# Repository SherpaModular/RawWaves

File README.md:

## Raw Waves v2

Raw Waves v2 is a sample player that functions much like a live radio. Audio sample files may be placed on a MicroSD card, and arranged into "banks" (like channels) which you may select either manually through the panel knobs, or via CV. File formats supported include RAW and WAV files.

The module is functionally identical to the popular "Raw Waves" module, and its predecessor, "Radio Music" by Tom Whitwell of Music Thing Modular. These previous modules are no longer available, having been built upon the now-discontinued Teensy 3 microcontroller.

Raw Waves v2 has been completely redesigned to use the Teensy 4 platform. Because the module uses the Teensy 4 microcontroller, the "Raw Waves v2" will not be compatible with other alternative firmware made for Radio Music (e.g. 'Chord Organ').

Raw Waves v2 still supports all of the settings in the SETTINGS.TXT file that you came to know and love in the earlier models. If you haven't played with the settings, you really should!

#### Specifications
Audio output: 16-bit audio output, with hardware anti-alias filtering.
Dimensions: 4 hp, 21mm deep.
Power specifications: Requires +12v (at 100 mA) and -12v (at 10 mA). The module features several protections against accidental reverse power connection: First, a keyed 10-pin Eurorack standard connector, second, automatically resetting fuses, and thirdly, protection diodes.
CV Inputs are designed for 0-5v, with reasonable over/undervoltage protection built-in.

#### Compiling the code
My preference is to use Visual Studio Code:
1. Install the Microsoft "Arduino for Visual Studio Code" extension
2. Add the Teensy packages. You can accomplish this in the "Arduino for Visual Studio Code" extension settings by adding the URL https://www.pjrc.com/teensy/package_teensy_index.json to the "Arduino: Additional Urls, Additional URLs for 3rd party packages." setting.
3. The following file contents, placed into the repo under the filename .vscode\arduino.json helps with other details:
```
{
    "sketch": "Software\\RawWavesV2\\RawWavesV2.ino",
    "configuration": "usb=serial,speed=600,opt=o2std,keys=en-us",
    "board": "teensy:avr:teensy40",
    "output": "ArduinoOutput\\RawWavesV2",
    "port": "COM3"
}
```
4. In VS Code, activate the Command Palette (typically by pressing F1), and choose "Ardunio: Verify".
5. If all codes well, the compiled output should appear in the repo directory, under ArduinoOutput\RawWavesV2

#### License  
Raw Waves is Open Hardware. It is a derivate work of ["Radio Music", by Tom Whitwell](https://github.com/TomWhitwell/RadioMusic). 
All hardware and software design in this project is Creative Commons licensed by Jim Mulvey: [CC-BY-SA: Attribution / ShareAlike](https://creativecommons.org/licenses/by-sa/3.0/)
If you use any work in this project, you should credit Tom Whitwell and me, and you must republish any changes you make under the same license.
This license does permit commercial use of these designs, but consider getting in touch before selling anything.
This project includes work from the [Teensy](https://www.pjrc.com/teensy/) project, which is not covered by this license.

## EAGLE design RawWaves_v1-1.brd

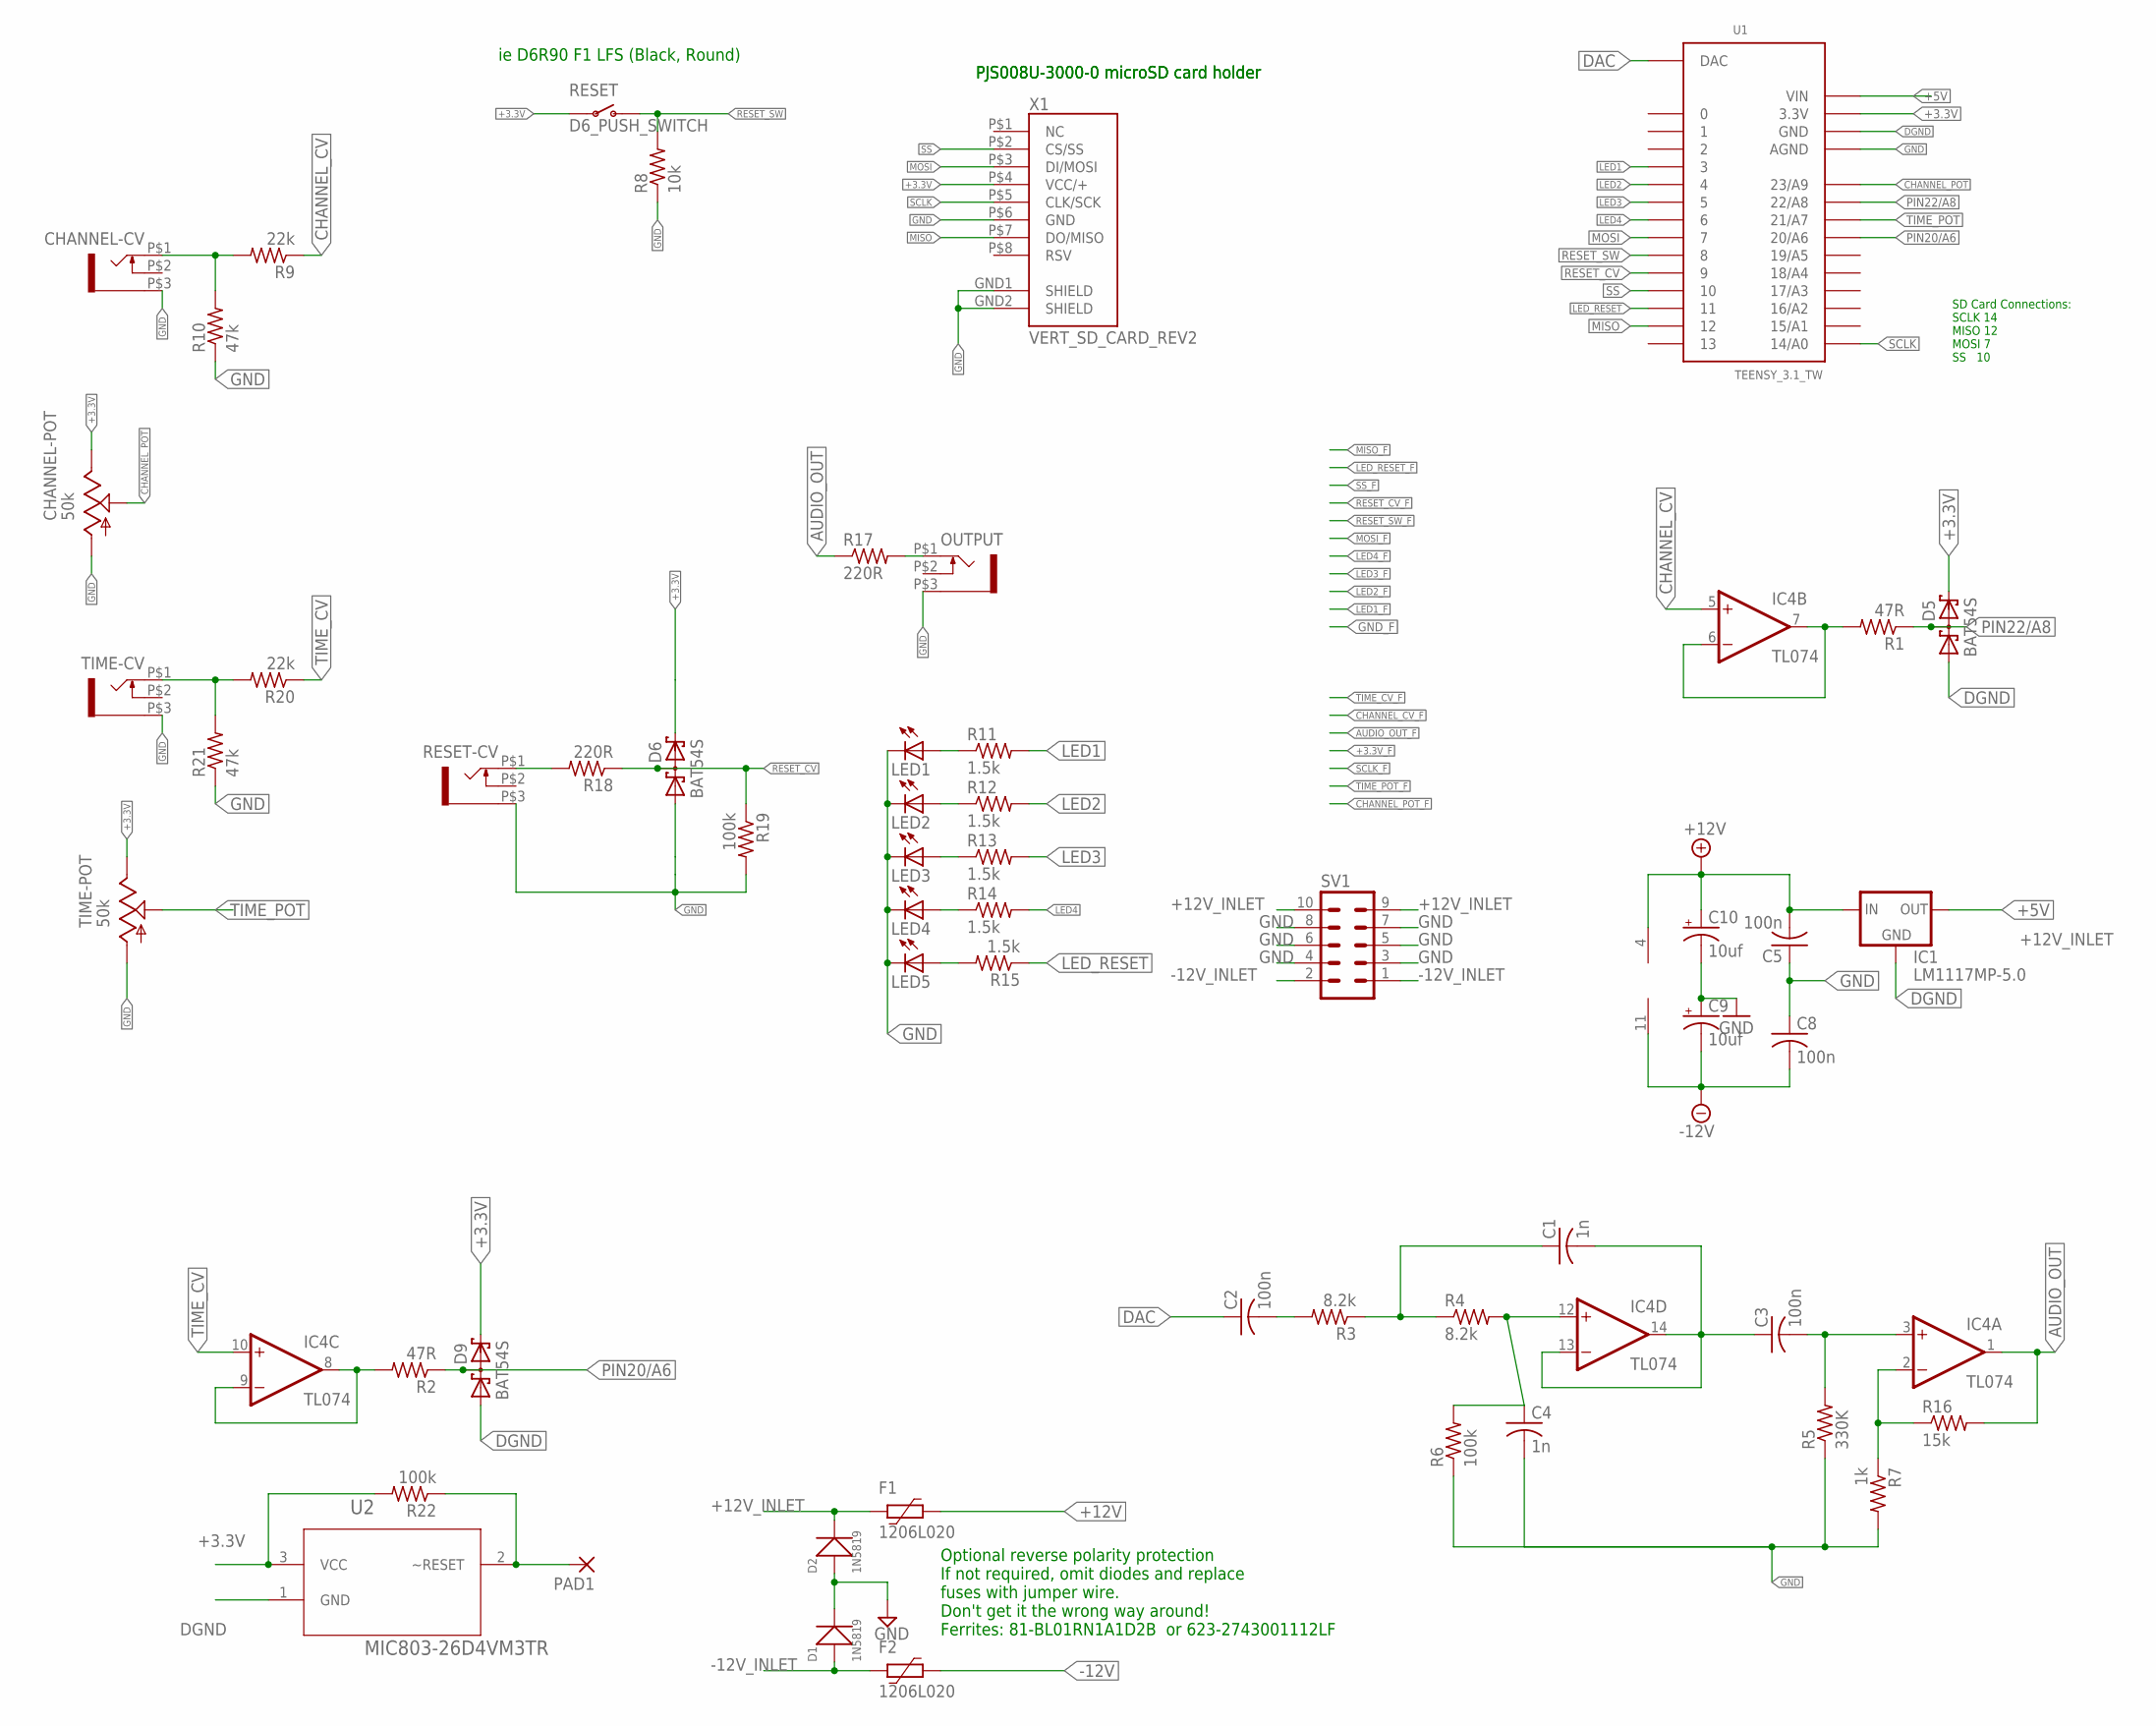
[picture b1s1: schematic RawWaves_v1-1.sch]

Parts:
C1, C4: 1n; C0805
C2, C3, C5, C8: 100n; C0805
C9, C10: 10uf; PANASONIC_B
CHANNEL-CV: WQP-PJ301M-12_JACK
CHANNEL-POT: 50k; EVUF
D1, D2: 1N5819; SOD-123
D5, D6, D9: BAT54S; SOT23
F1, F2: 1206L020; 1206L
IC1: LM1117MP-5.0; SOT223
IC4: TL074; SO14
LED1, LED2, LED3, LED4, LED5: LED3MM
OUTPUT: WQP-PJ301M-12_JACK
PAD1: 1,6/0,9
R1, R2: 47R; R0805
R3, R4: 8.2k; R0805
R5: 330K; R0805
R6, R19, R22: 100k; R0805
R7: 1k; R0805
R8: 10k; R0805
R9, R20: 22k; R0805
R10, R21: 47k; R0805
R11, R12, R13, R14, R15: 1.5k; R0805
R16: 15k; R0805
R17, R18: 220R; R0805
RESET: D6_PUSH_SWITCH; D6_BUTTON_RND
RESET-CV: WQP-PJ301M-12_JACK
SV1: 10_PIN_HEADER; MA05-2
TIME-CV: WQP-PJ301M-12_JACK
TIME-POT: 50k; EVUF
U1: TEENSY_3.1_TW
U2: MIC803-26D4VM3TR; SOT95P232X110-3N
X1: VERT_SD_CARD_REV2; VERT_MICROSD_REV2

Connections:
+3.3V: CHANNEL-POT.3 (E), D5.2 (C2), D6.2 (C2), D9.2 (C2), R22.2, RESET.P$3, RESET.P$4, TIME-POT.3 (E), U1.3.3V, U2.3 (VCC), X1.P$4 (VCC/+)
+5V: IC1.2 (OUT), IC1.4 (OUT), U1.VIN
+12V: C5.2, C10.+, F1.1, IC1.3 (IN), IC4.4 (V+)
+12V_INLET: D2.-, F1.2, SV1.9, SV1.10
-12V: C8.2, C9.-, F2.1, IC4.11 (V-)
-12V_INLET: D1.+, F2.2, SV1.1, SV1.2
AUDIO_OUT: IC4.1 (OUT), R16.2, R17.1
CHANNEL_CV: IC4.5 (+IN), R9.1
CHANNEL_POT: CHANNEL-POT.2 (S), U1.23/A9
DAC: C2.1, U1.DAC
DGND: D5.1 (A1), D9.1 (A1), IC1.1 (GND), U1.GND, U2.1 (GND)
GND: C4.2, C5.1, C8.1, C9.+, C10.-, CHANNEL-CV.P$3 (1), CHANNEL-POT.1 (A), D1.-, D2.+, D6.1 (A1), LED1.K (C), LED2.K (C), LED3.K (C), LED4.K (C), LED5.K (C), OUTPUT.P$3 (1), R5.1, R6.1, R7.2, R8.1, R10.1, R19.2, R21.1, RESET-CV.P$3 (1), SV1.3, SV1.4, SV1.5, SV1.6, SV1.7, SV1.8, TIME-CV.P$3 (1), TIME-POT.1 (A), U1.AGND, X1.GND1 (SHIELD), X1.GND2 (SHIELD), X1.P$6 (GND)
LED1: R11.2, U1.3
LED2: R12.2, U1.4
LED3: R13.2, U1.5
LED4: R14.2, U1.6
LED_RESET: R15.1, U1.11
MISO: U1.12, X1.P$7 (DO/MISO)
MOSI: U1.7, X1.P$3 (DI/MOSI)
unnamed: IC4.6 (-IN), IC4.7 (OUT), R1.2
unnamed: C4.1, IC4.12 (+IN), R4.2, R6.2
unnamed: OUTPUT.P$1 (2), R17.2
unnamed: C1.1, R3.1, R4.1
unnamed: C1.2, C3.1, IC4.13 (-IN), IC4.14 (OUT)
unnamed: C3.2, IC4.3 (+IN), R5.2
unnamed: IC4.2 (-IN), R7.1, R16.1
unnamed: IC4.8 (OUT), IC4.9 (-IN), R2.2
unnamed: CHANNEL-CV.P$1 (2), R9.2, R10.2
unnamed: C2.2, R3.2
unnamed: LED2.A, R12.1
unnamed: LED4.A, R14.1
unnamed: LED3.A, R13.1
unnamed: R18.2, RESET-CV.P$1 (2)
unnamed: LED1.A, R11.1
unnamed: LED5.A, R15.2
unnamed: PAD1.1, R22.1, U2.2 (~RESET)
PIN20/A6: D9.3 (C1A2), R2.1, U1.20/A6
PIN22/A8: D5.3 (C1A2), R1.1, U1.22/A8
RESET_CV: D6.3 (C1A2), R18.1, R19.1, U1.9
RESET_SW: R8.2, RESET.P$1 (O), RESET.P$2 (O), U1.8
SCLK: U1.14/A0, X1.P$5 (CLK/SCK)
SS: U1.10, X1.P$2 (CS/SS)
TEMP: R20.2, R21.2, TIME-CV.P$1 (2)
TIME_CV: IC4.10 (+IN), R20.1
TIME_POT: TIME-POT.2 (S), U1.21/A7

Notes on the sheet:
ie D6R90 F1 LFS (Black, Round)
PJS008U-3000-0 microSD card holder
SD Card Connections: SCLK 14 MISO 12 MOSI 7 SS 10
Optional reverse polarity protection If not required, omit diodes and replace fuses with jumper wire. Don't get it the wrong way around! Ferrites: 81-BL01RN1A1D2B or 623-2743001112LF

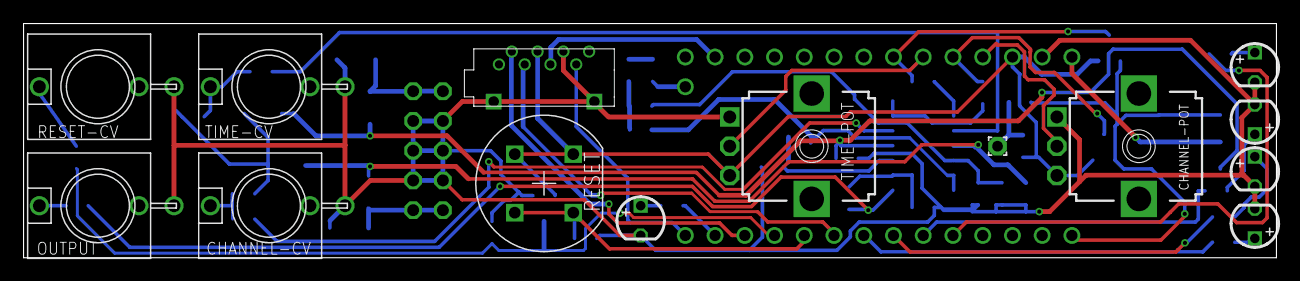
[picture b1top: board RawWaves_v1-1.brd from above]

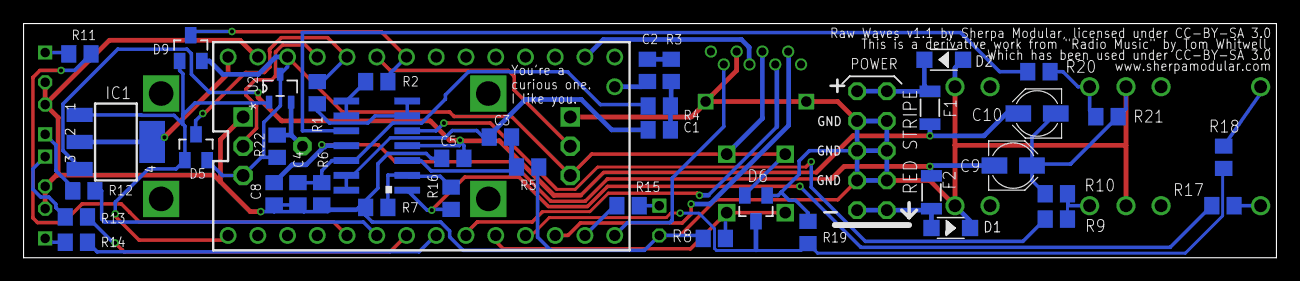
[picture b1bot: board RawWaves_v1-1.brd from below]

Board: 4 copper layers, 107.0 x 20.0 mm, 56 parts (42 on the bottom side), 45 nets.

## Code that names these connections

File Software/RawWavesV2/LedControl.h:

#ifndef LedControl_h
#define LedControl_h

/**
 * Raw Waves LED control
 *
 * 4 LEDs across the top and 1 reset LED.
 *
 */
#define LED0 2 // was 6 before PCB change
#define LED1 3 // was 5 before PCB change
#define LED2 4
#define LED3 5 // was 3 before PCB change
#define RESET_LED 6 // Reset LED indicator. Was 11 in Teensy 3.2 but conflicts with the SD card in Teensy 4 // was 2 before PCB change

class LedControl {

	public:
		void init();
		void single(int index);
		void multi(uint8_t bits);
		void showReset(boolean high);

};
#endif

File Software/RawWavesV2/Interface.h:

#ifndef Interface_h
#define Interface_h

#include <Arduino.h>
#include <Bounce2.h>
#include "PlayState.h"
#include "Settings.h"
#include "AnalogInput.h"

#define CHAN_POT_PIN A0 	// pin for Station pot (aka Channel pot), was A9 in Teensy 3.2 version
#define CHAN_CV_PIN A1 		// pin for Station CV (aka Channel CV), was A6 in Teensy 3.2 version
#define TIME_POT_PIN A5 	// pin for Start pot (aka Time pot), was A7 in Teensy 3.2 version
#define TIME_CV_PIN A8 		// pin for Start CV (aka Time CV)
#define RESET_BUTTON 8 		// Reset button
#define RESET_CV 9 		    // Reset pulse input

#define TIME_POT_CHANGED 	1       //binary 000000000001
#define TIME_CV_CHANGED 	1 << 1  //binary 000000000010
#define CHANNEL_CHANGED 	1 << 2  //binary 000000000100
#define CHANGE_START_NOW 	1 << 3  //binary 000000001000
#define BUTTON_SHORT_PRESS 	1 << 4  //binary 000000010000
#define BUTTON_LONG_PRESS 	1 << 5  //binary 000000100000
#define BUTTON_LONG_RELEASE 1 << 6  //binary 000001000000
#define BUTTON_PULSE 		1 << 7  //binary 000010000000 Note: A BUTTON_PULSE is a long press that is held for longer than LONG_PRESS_DURATION
#define RESET_TRIGGERED 	1 << 8  //binary 000100000000
#define ROOT_CV_CHANGED		1 << 9  //binary 001000000000
#define ROOT_POT_CHANGED	1 << 10 //binary 010000000000
#define ROOT_NOTE_CHANGED	1 << 11 //binary 100000000000

#define SHORT_PRESS_DURATION 10
#define LONG_PRESS_DURATION 600
// after LONG_PRESS_DURATION every LONG_PRESS_PULSE_DELAY milliseconds the update
// function will set BUTTON_PULSE
#define LONG_PRESS_PULSE_DELAY 600

#define SAMPLEAVERAGE   16 	// How many values are read and averaged of pot/CV inputs each interface check.

class Interface {
public:
	boolean quantiseRootCV = true;
	boolean quantiseRootPot = true;

	float rootNoteCV = 36;
	float rootNotePot = 36;
	float rootNote = 36;

	//boolean buttonHeld = false;
	unsigned long start = 0;

	elapsedMillis buttonHoldTime;

	PlayState* playState;

	Interface() : channelCVInput(CHAN_CV_PIN),
			channelPotInput(CHAN_POT_PIN),
			startCVInput(TIME_CV_PIN),
			startPotInput(TIME_POT_PIN)
	{
		playState = NULL;
	}

	void init(int fileSize, int channels, const Settings& settings, PlayState* state);
	void setChannelCount(uint16_t count);

	uint16_t update();
	uint16_t updateButton();
private:
	AnalogInput channelCVInput;
	AnalogInput channelPotInput;
	AnalogInput startCVInput;
	AnalogInput startPotInput;

	Bounce2::Button resetButton;
	elapsedMillis buttonTimer = 0;

	uint16_t changes = 0;

	uint16_t startCVDivider = 1;
	boolean channelPotImmediate = true;
	boolean channelCVImmediate = true;
	boolean startPotImmediate = true;
	boolean startCVImmediate = true;

	uint16_t channelCount = 0;
	float rootNoteOld = -100;
	float rootNotePotOld = -100;
	float rootNoteCVOld = -100;

	uint16_t updateChannelControls();
	uint16_t updateStartControls();
	uint16_t updateRootControls();
	boolean pitchMode = false;
};

#endif

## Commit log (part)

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2021-02-24 Add Voltage Supervisor
2021-02-24 Widen Pogo Hole
    Replaced "Pogo 1.6/0.8" with "Pogo 1.6/0.9"
2023-07-02 Remove old v1 files
2023-07-16 Add final v2 schematic, PCB, BOM and software
2023-07-16 Add README with license
2023-07-17 Add compile instructions; ino file must match parent folder
2025-05-16 'Button' does not name a type
    Intended to fix #6

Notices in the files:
RawWaves_v1-1.brd:
Raw Waves v1.1 by Sherpa Modular, licensed under CC-BY-SA 3.0
This is a derivative work from "Radio Music" by Tom Whitwell,
Which has been used under CC-BY-SA 3.0
parts and their libraries:
lm1117: (c) 2014 Samuel Lourenço
